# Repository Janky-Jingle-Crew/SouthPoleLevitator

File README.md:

# South Pole Levitator

Janky Jingle Crew is back this Christmas as well! We are continuing with the theme of magnetic propulsion from last year, but this time for levitation! 

## Background
Magnetic levitation kits have been around for a long time, but most of them are analog designs running on 12 V. A more recent 5 V digital version by [Jonathan Lock](https://gitlab.com/e4870/maglev/-/tree/main) caught our attention and served as a big source of inspiration for this project. Our take focuses on lowering the BOM cost and making assembly easier by replacing traditional coils with PCB coils.

We were aiming to build a batch of around 50 units, so coil winding quickly became a bottleneck. That led us to PCB coils as a more scalable solution. Mounting the coils was another pain point, gluing them down and then soldering wires (like many existing kits do) felt messy. Instead, we combined the mounting and electrical connection using solderable standoffs.

We also made a (slightly unnecessary) optimization on the microcontroller side. To reduce BOM cost slightly, we chose the STM32G030, which doesn’t have an FPU, and planned to implement all control algorithms using fixed-point math. In hindsight, the time spent probably outweighed the cost savings, but at least we learned a lot about fixed-point math (and wrote terrible code) along the way.

The final result is shown below: a fully functional magnetic levitation platform made entirely from PCBs. Even the levitating tree is a PCB. Overall, the project turned out well, although there are plenty of things that could still be improved. Feel free to open an issue or mail us if you have any technical questions.

<!--  -->

## User Guide

The card needs to be powered with a 5V power supply over USB-C, capable of at least 500 mA.

To levitate the tree:

1. Place the tree away from the driver board.
2. Place the driver board on a flat, nonmagnetic surface, and plug in the USB-C cable. Note that the board needs to be level when it gets power for the correct calibration. If the tree is too close, this will also affect the calibration. The calibration is complete once you hear a short beep from the coils. The status LED should also start blinking.
3. Hold the tree a few centimeters over and lower it slowly, trying to keep it centered and pointed straight up.
4. The rest is a balance between keeping the tree centered, and holding it with a loose enough grip. The tree needs to have the freedom to find the center itself, while also being prevented from sticking to either of the four base magnets.

It is also possible to play some Christmas tunes. Simply turn the driver board upside down and place the tree on top of it. The coils should start playing a random assortment of Christmas tunes.

## Working principle

### Magnetic levitation
The levitation is generated by four PCB coils but also four neodymium magnets. The base magnets provide the majority of the force required for levitation while the coils only generate a small corrective force required to keep the magnet in a stable position (Earnshaw's theorem). 

Each coil can be driven independently, but we chose to split the coils into two pairs (X & Y) and drive them with opposite polarity.

A 3D Hall effect sensor TMAG5273 was used to sense the position of the levitating magnet and drive the coils accordingly.

### Control

At the core the control algorithm is a PD controller controlling the duty cycle of the coil drivers in order to keep the levitating magnet centered in the X and Y direction. The position is not directly measured, instead the magnetic field strength in the X and Y direction is used as a proxy for position. This is not linear with the actual position, but is approximated as linear close to the center. This is the general idea but there are multiple problems that need to be handled for stable levitation:
<!-- - Non-linear relation between coil driver duty cycle and generated magnetic field. -->
<!-- - Non-linear coil driver characteristics. -->
<!-- - Coupling between coil current and measured magnetic field. -->
<!-- - Setpoint calibration. -->

<details>
<!-- #### Non-linear coil driver characteristics. -->
<summary> Non-linear coil driver characteristics </summary>

We observed a non linear relation between the coil driver duty cycle and the output current which can be seen in the figure below. To correct for this we wanted to measure the coil current as a function of duty cycle. Since coil current is proportional to the generated magnetic field we can measure the strength of the magnetic field for different duty cycles with the hall sensor. From this a quadratic fit was made which is used to linearize the coil driver response in the control algorithm.

</details>

<details>
<!-- #### Coil coupling compensation -->
<summary> Coupling between coil current and measured magnetic field </summary>

When driving the coils, the generated magnetic field affects the hall sensor measurements. This is problematic since this is added to the field from the levitating magnet and affects the position measurement. Since the position measurement is used as the input to the controller this creates a feedback loop which can lead to instability and oscillations. To compensate for this an feedforward model of the generated magnetic field from the coil current is subtracted from the hall sensor measurements before they are used in the controller. This model is created by measuring the magnetic field from each coil at different duty cycles while there is no levitating magnet present. A linear fit is then made to get the coupling coefficients for each coil. This is done during the initialization of the system.

</details>

<details>
<!-- #### Setpoint calibration -->
<summary> Setpoint calibration </summary>

Due to manufacturing tolerances in the placement of the hall sensor and the base magnets, the center of the base magnetic field, which is the optimal place to levitate the magnet, does not necessarily correspond to above the hall sensor. This means that the setpoint for the controller has to be calibrated for each unit.

In the figure above, an illustrative example of the magnetic potential from the base magnets and the proportional part of the PD controller is shown. The blue curve represents the potential from the base magnets, which has a unstable equilibrium point at $x_{base}=1$. The orange curve represents the potential from the proportional part of the controller, which is centered around the setpoint at $x_{setpoint} = 0$. The total potential is the sum of these two potentials, shown in green, which has a stable equilibrium point close to but not exactly at the setpoint. Due to the slope of the base potential at the setpoint, the equilibrium point will be offset the setpoint away from the base magnet center. By calculating this difference $x_{delta} = x_{equilibrium} - x_{setpoint}$ we can then adjust the setpoint $x_{setpoint,new} = x_{setpoint} + \alpha x_{delta}$ to move the equilibrium point closer to the setpoint. This process is repeated every control loop and will lead to the setpoint converging to the base magnet center.

</details>

### Driving LEDs wirelessly

The LEDs on the tree are powered by electro-magnetic noise from the switching ripple of the coils on the driver board. There are four PCB coils in the base of the tree, each powering its quarter. The induced AC voltage in each of these coils is amplified with a resonant LC-tank tuned to the switching frequency. The resonance circuit consists of the inductance in the PCB coil and a separate MLCC C0G capacitor on the tree quarter. This amplified waveform is then rectified with a single Schottky diode, finally driving the LEDs. The power transfer efficiency is absolutely garbage and therefore the LEDs will only light up when the coils are aligned. However, this also gives a passive blinking/strobing effect when it spins (without any additional components)! Definitely a planned feature and not a design flaw....

## Design
The whole levitator can be split into two main parts. The platform base and the levitating tree. The platform base consists of two different PCB designs, one driver PCB and four coil PCBs (4x).

### Driver board
The driver board has all the components mounted. There are a total of 12 standoffs: 8x M2 standoffs for mounting the coil board and 4x M3 standoffs for mounting the base magnets. An STM32G030 reads the XYZ magnetic fields from the TMAG5273 and controls 4x DRV8837 drivers for the coils. Power is provided by USB-C connector. A TagConnect TC2030 along with pin headers break out the SWD pins for debugging.

### Coil board
The coil board consists of four spiral coils with ~116 turns and 0.245mm trace width (25 turns per layer, 4-layer PCB, outer 1 oz, inner 1 oz). The resulting coil resistance turns out to be around 20 Ohm. Therefore, 4x coils are connected in parallel to enable higher coil current and also increase efficiency slightly. Brass washers are placed in-between each coil board to ensure electrical contact all the way down to the driver board. Initially a coil with 100 turns and 0.3mm trace width was used (outer 1 oz, inner 0.5 oz). This worked fine as well and 0.5oz is way cheaper. You can use either one, although the code might be slightly more tuned for the 116 turns variant, it should still work with the cheaper 100 turns variant.

### Tree
The tree consists of 5 PCBs, four of which constitute the tree itself, and one being the base plate with the pickup coils. A 3D-printed star keeps all of the tree-PCBs connected at the top! Tip: blow on one side of the tree when it is levitating to make it spin!

## Manufacturing
All the manufacturing files for the PCBs and the final software can be found in this repository. 

Upload these to your favorite PCB manufacturer and order the boards. We designed the boards with JLCPCBs preexisting Parts Lib and used their PCBA due to time constraints. However, PCBWay and NextPCB probably have these components in stock as well or can source them for you.

You will also need the following materials per unit:
- 1x Levitation magnet (N35-N45 30mm diameter, 10mm height) 
- 4x Ring magnets with M3 countersunk hole (N35-N45, 12mm diameter, 5mm height)
- 8x Non-magnetic M2 screws 8mm
- 4x Non-magnetic M3 countersunk screws 8mm
- 24x M2 Brass washers 4-5mm OD (steel probably works as well, slightly worse conductivity).
- 8x Rubber feet (at least 0.4mm height)

## Assembly

### Driver board

### Tree

To begin with, the star is 3D-printed. You can either use the half-star variant (recommended) or the whole-star variant. For the half-star, print two of them laying flat and with support activated. The halves can then be glued together with superglue. Alternatively, the whole-star variant can be printed standing up depending on how well your printer handles overhang and/or surface finishes over supports.

To keep the magnet centered, and the parts of the tree perpendicular to the base, a 3D-printed jig was used. This is not necessary, but drastically reduces the time to assemble multiple trees. If you are only making one, don't bother printing out the jig.

Both the magnet and the star can be glued with e.g. superglue or epoxy. Note that the magnet orientation matters!

The four "quarters" of the tree are soldered onto the base PCB with two solder joints each. These joints are the PCB coil A & B. We recommend gluing the star before soldering!

## FAQ

### How do I reproduce this?
PCB assembly files can be found in /production for the driver board and tree in their respective folders under PCB/. 
Gerber files for both coil boards are found in /gerber in their respective folders under PCB/. Remember to choose 1oz inner layers if you go for 116 turns variant.
Upload to your PCB manufacture of choice (JLCPCB, PCBWay, NextPCB).
Print the star. Buy magnets and screws. Assemble.

#### Flashing
An STLink, Segger Jlink or similar is required to flash the driver board. Some type of 6 pin (2x3 1.27mm pitch) pogo connector is also required (we use a TagConnect TC2030NL).
Or you can use the through hole SWD pins. A compiled binary is provided in SW/release if you don't want to go through the hassle of compiling yourself because the makefile is a bit of mess currently. It's written for a Windows filesystem but uses unix commands (we used msys2 or cmder to compile). Next project will probably use cmake to avoid these problems.

### How much did this all cost?
This year's project was quite expensive. Even with a big batch of 50 units, the unit cost was around 40-50 EUR. PCBs alone cost 20 EUR per unit. Magnets and screws were not cheap either.
Expect to spend quite a bit if you are planning on reproducing it, especially a small batch. 

## Acknowledgements
Special thanks to Jonathan Lock, this project was heavily inspired by his well-documented [maglev build](https://gitlab.com/e4870/maglev/-/tree/main).

Also thanks to Seth.K and his [coil generator plugin for KiCAD](https://github.com/SK-Electronics-Consulting/kicad-coil-generators). 

## Credits
The Janky Jingle Crew 2025 consists of:

 - [Daniel Quach](https://github.com/BasementCircuits): Project lead, PCB, Firmware
 - [Johan Wheeler](https://github.com/johanwheeler): Firmware, Control
 - [Gustav Abrahamsson](https://github.com/GustavAbrahamsson): PCB, Mechanical
 - [Adam Anderson](https://github.com/adaand00): Firmware

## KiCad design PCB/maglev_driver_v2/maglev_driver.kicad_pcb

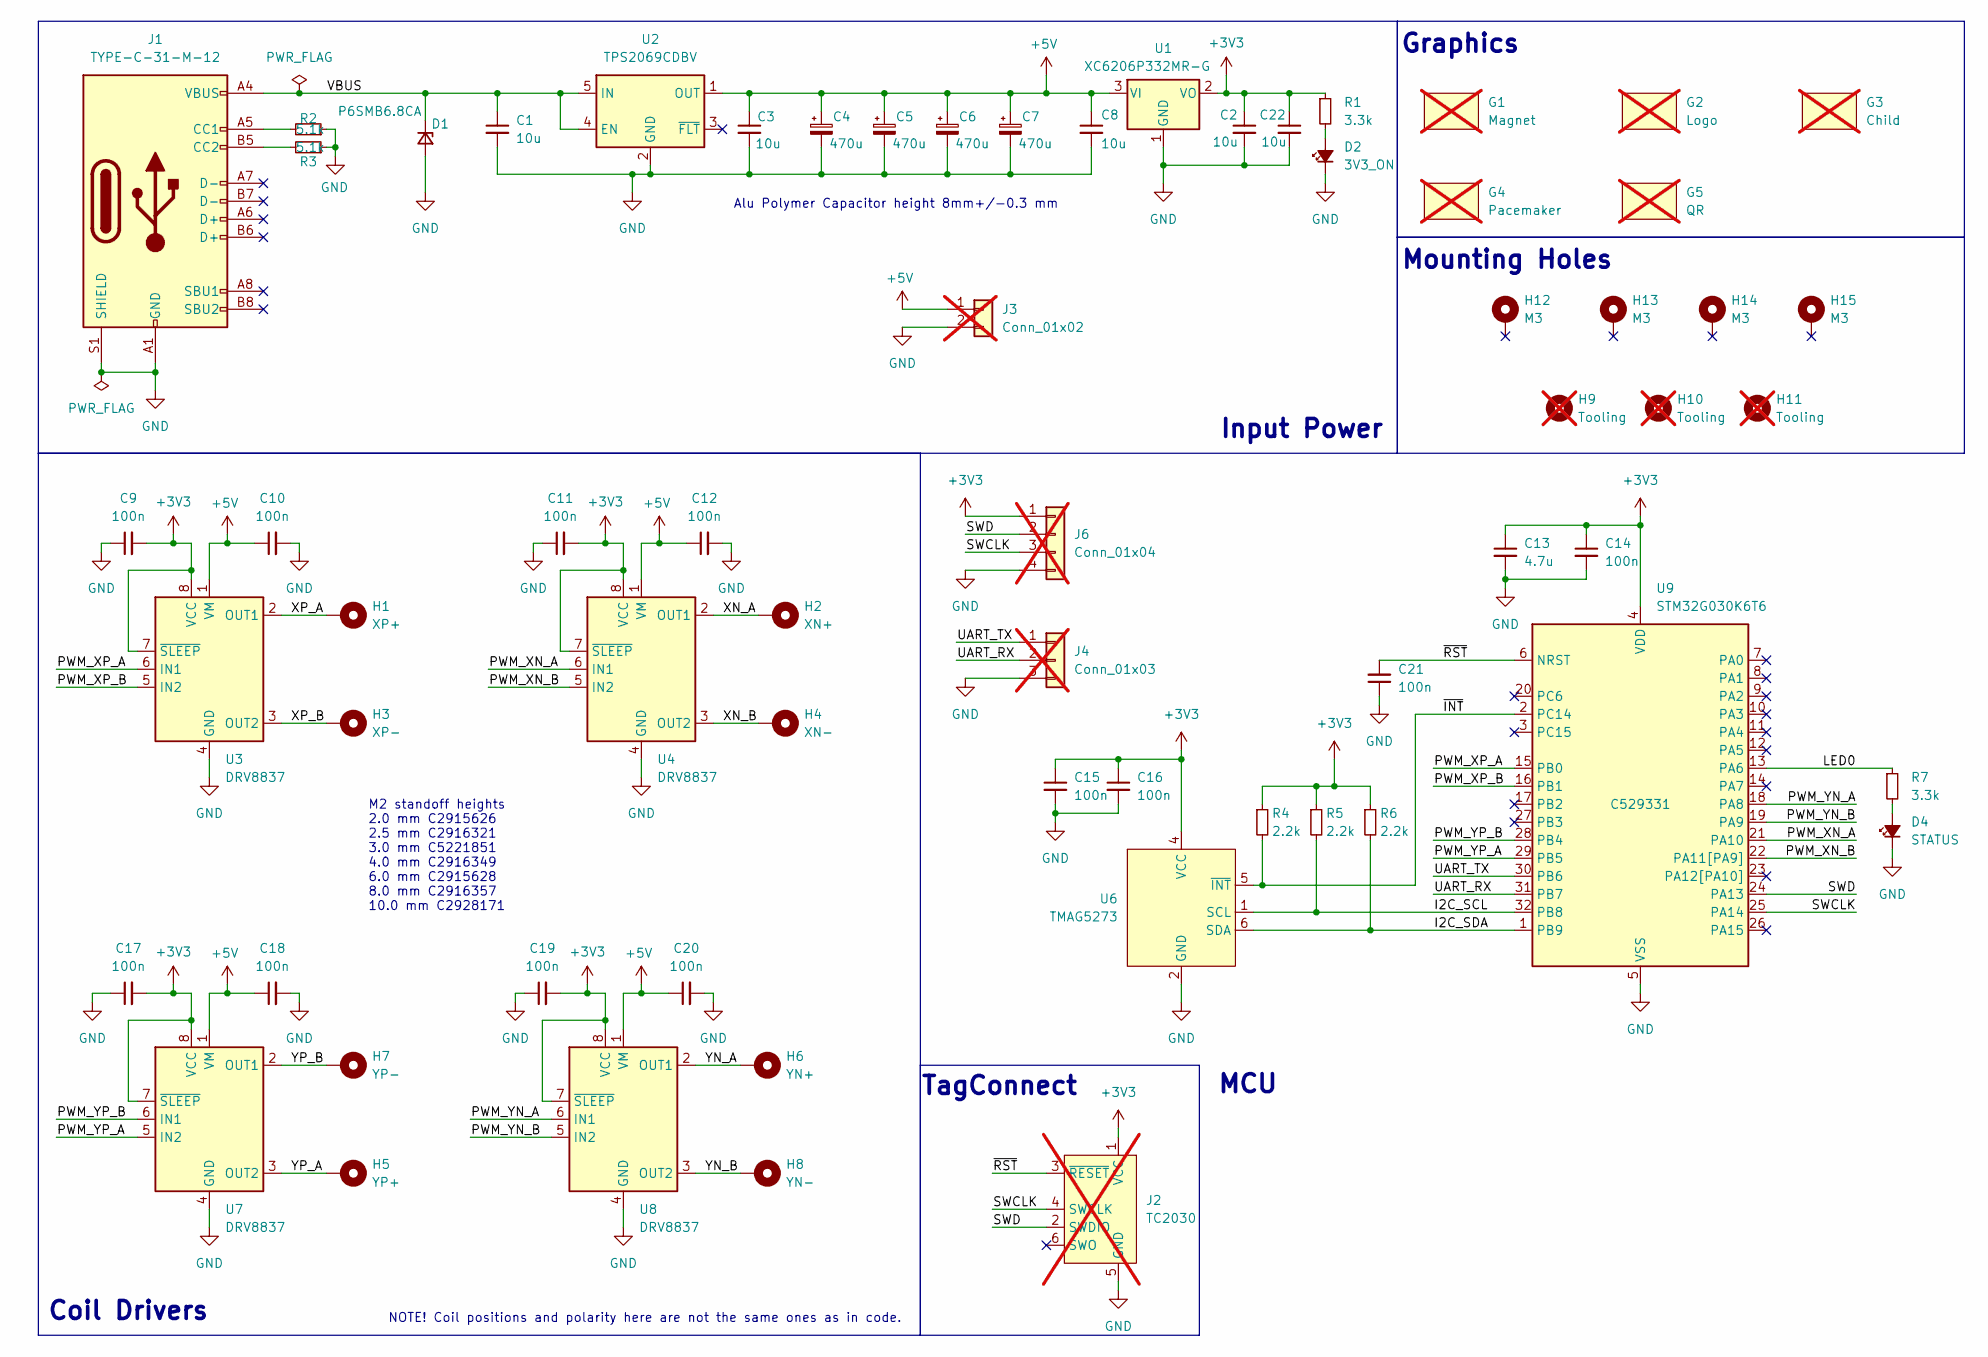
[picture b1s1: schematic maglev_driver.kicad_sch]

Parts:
C1, C2, C3, C8, C22: 10u; C_1206_3216Metric; MPN C13585
C4, C5, C6, C7: 470u; C_Elec_6.3x7.7; MPN C46550459
C9, C10, C11, C12, C14, C15, C16, C17, C18, C19, C20, C21: 100n; C_0402_1005Metric; MPN C307331
C13: 4.7u; C_1206_3216Metric; MPN C29823
D1: P6SMB6.8CA; D_SMB; MPN C78395
D2: 3V3_ON; LED_0805_2012Metric; MPN C2296
D4: STATUS; LED_0805_2012Metric; MPN C2297
G1: Magnet; mag_warning_7_7_mm; not fitted
G2: Logo; tree_7_9; not fitted
G3: Child; child_warning_7_8_mm; not fitted
G4: Pacemaker; pacemaker_warning_7_7_mm; not fitted
G5: QR; qr_25mm; not fitted
H1: XP+; SMTSO20; MPN C2928171
H2: XN+; SMTSO20; MPN C2928171
H3: XP-; SMTSO20; MPN C2928171
H4: XN-; SMTSO20; MPN C2928171
H5: YP+; SMTSO20; MPN C2928171
H6: YN+; SMTSO20; MPN C2928171
H7: YP-; SMTSO20; MPN C2928171
H8: YN-; SMTSO20; MPN C2928171
H9, H10, H11: Tooling; tooling_hole; not fitted
H12, H13, H14, H15: M3; SMTSO30; MPN C2915635
J1: TYPE-C-31-M-12; USB_C_Receptacle_HRO_TYPE-C-31-M-12; MPN C165948
J2: TC2030; Tag-Connect_TC2030-IDC-NL_2x03_P1.27mm_Vertical; not fitted
J3: Conn_01x02; PinHeader_1x02_P2.54mm_Vertical; not fitted
J4: Conn_01x03; PinHeader_1x03_P2.54mm_Vertical; not fitted
J6: Conn_01x04; PinHeader_1x04_P2.54mm_Vertical; not fitted
R1, R7: 3.3k; R_0402_1005Metric; MPN C25890
R2, R3: 5.1k; R_0603_1608Metric; MPN C23186
R4, R5, R6: 2.2k; R_0402_1005Metric; MPN C25879
U1: XC6206P332MR-G; SOT-23-3; MPN C5446
U2: TPS2069CDBV; SOT-23-5; MPN C181752
U3, U4, U7, U8: DRV8837; WSON-8-1EP_2x2mm_P0.5mm_EP0.9x1.6mm; MPN C39159
U6: TMAG5273; SOT-23-6; MPN C3716049
U9: STM32G030K6T6; LQFP-32_7x7mm_P0.8mm; MPN C529331

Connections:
+3V3: C2.1, C9.2, C11.2, C13.1, C14.1, C15.1, C16.1, C17.2, C19.2, C22.1, J2.1 (VCC), J6.1, R1.1, R4.1, R5.1, R6.1, U1.2 (VO), U3.7 (~SLEEP), U3.8 (VCC), U4.7 (~SLEEP), U4.8 (VCC), U6.4 (VCC), U7.7 (~SLEEP), U7.8 (VCC), U8.7 (~SLEEP), U8.8 (VCC), U9.4 (VDD)
+5V: C3.1, C4.1, C5.1, C6.1, C7.1, C8.1, C10.1, C12.1, C18.1, C20.1, J3.1, U1.3 (VI), U2.1 (OUT), U3.1 (VM), U4.1 (VM), U7.1 (VM), U8.1 (VM)
/I2C_SCL: R5.2, U6.1 (SCL), U9.32 (PB8)
/I2C_SDA: R6.2, U6.6 (SDA), U9.1 (PB9)
/LED0: R7.1, U9.13 (PA6)
/PWM_XN_A: U4.6 (IN1), U9.21 (PA10)
/PWM_XN_B: U4.5 (IN2), U9.22 (PA11[PA9])
/PWM_XP_A: U3.6 (IN1), U9.15 (PB0)
/PWM_XP_B: U3.5 (IN2), U9.16 (PB1)
/PWM_YN_A: U8.6 (IN1), U9.18 (PA8)
/PWM_YN_B: U8.5 (IN2), U9.19 (PA9)
/PWM_YP_A: U7.5 (IN2), U9.29 (PB5)
/PWM_YP_B: U7.6 (IN1), U9.28 (PB4)
/SWCLK: J2.4 (SWCLK), J6.3, U9.25 (PA14)
/SWD: J2.2 (SWDIO), J6.2, U9.24 (PA13)
/UART_RX: J4.2, U9.31 (PB7)
/UART_TX: J4.1, U9.30 (PB6)
/VBUS: C1.1, D1.1 (K), J1.A4 (VBUS), J1.A9 (VBUS), J1.B4 (VBUS), J1.B9 (VBUS), U2.4 (EN), U2.5 (IN)
/XN_A: H2.1, U4.2 (OUT1)
/XN_B: H4.1, U4.3 (OUT2)
/XP_A: H1.1, U3.2 (OUT1)
/XP_B: H3.1, U3.3 (OUT2)
/YN_A: H6.1, U8.2 (OUT1)
/YN_B: H8.1, U8.3 (OUT2)
/YP_A: H5.1, U7.3 (OUT2)
/YP_B: H7.1, U7.2 (OUT1)
/~INT: R4.2, U6.5 (~INT), U9.2 (PC14)
/~RST: C21.2, J2.3 (~RESET), U9.6 (NRST)
GND: C1.2, C2.2, C3.2, C4.2, C5.2, C6.2, C7.2, C8.2, C9.1, C10.2, C11.1, C12.2, C13.2, C14.2, C15.2, C16.2, C17.1, C18.2, C19.1, C20.2, C21.1, C22.2, D1.2 (A), D2.1 (K), D4.1 (K), J1.A1 (GND), J1.A12 (GND), J1.B1 (GND), J1.B12 (GND), J1.S1 (SHIELD), J2.5 (GND), J3.2, J4.3, J6.4, R2.1, R3.1, U1.1 (GND), U2.2 (GND), U3.4 (GND), U3.9 (GND), U4.4 (GND), U4.9 (GND), U6.2 (GND), U6.3 (GND), U7.4 (GND), U7.9 (GND), U8.4 (GND), U8.9 (GND), U9.5 (VSS)
unnamed: D2.2 (A), R1.2
unnamed: D4.2 (A), R7.2
unnamed: J1.A5 (CC1), R2.2
unnamed: J1.B5 (CC2), R3.2

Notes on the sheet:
NOTE! Coil positions and polarity here are not the same ones as in code.
MCU
Graphics
Coil Drivers
Alu Polymer Capacitor height 8mm+/-0.3 mm
M2 standoff heights 2.0 mm C2915626 2.5 mm C2916321 3.0 mm C5221851 4.0 mm C2916349 6.0 mm C2915628 8.0 mm C2916357 10.0 mm C2928171
Mounting Holes
TagConnect
Input Power

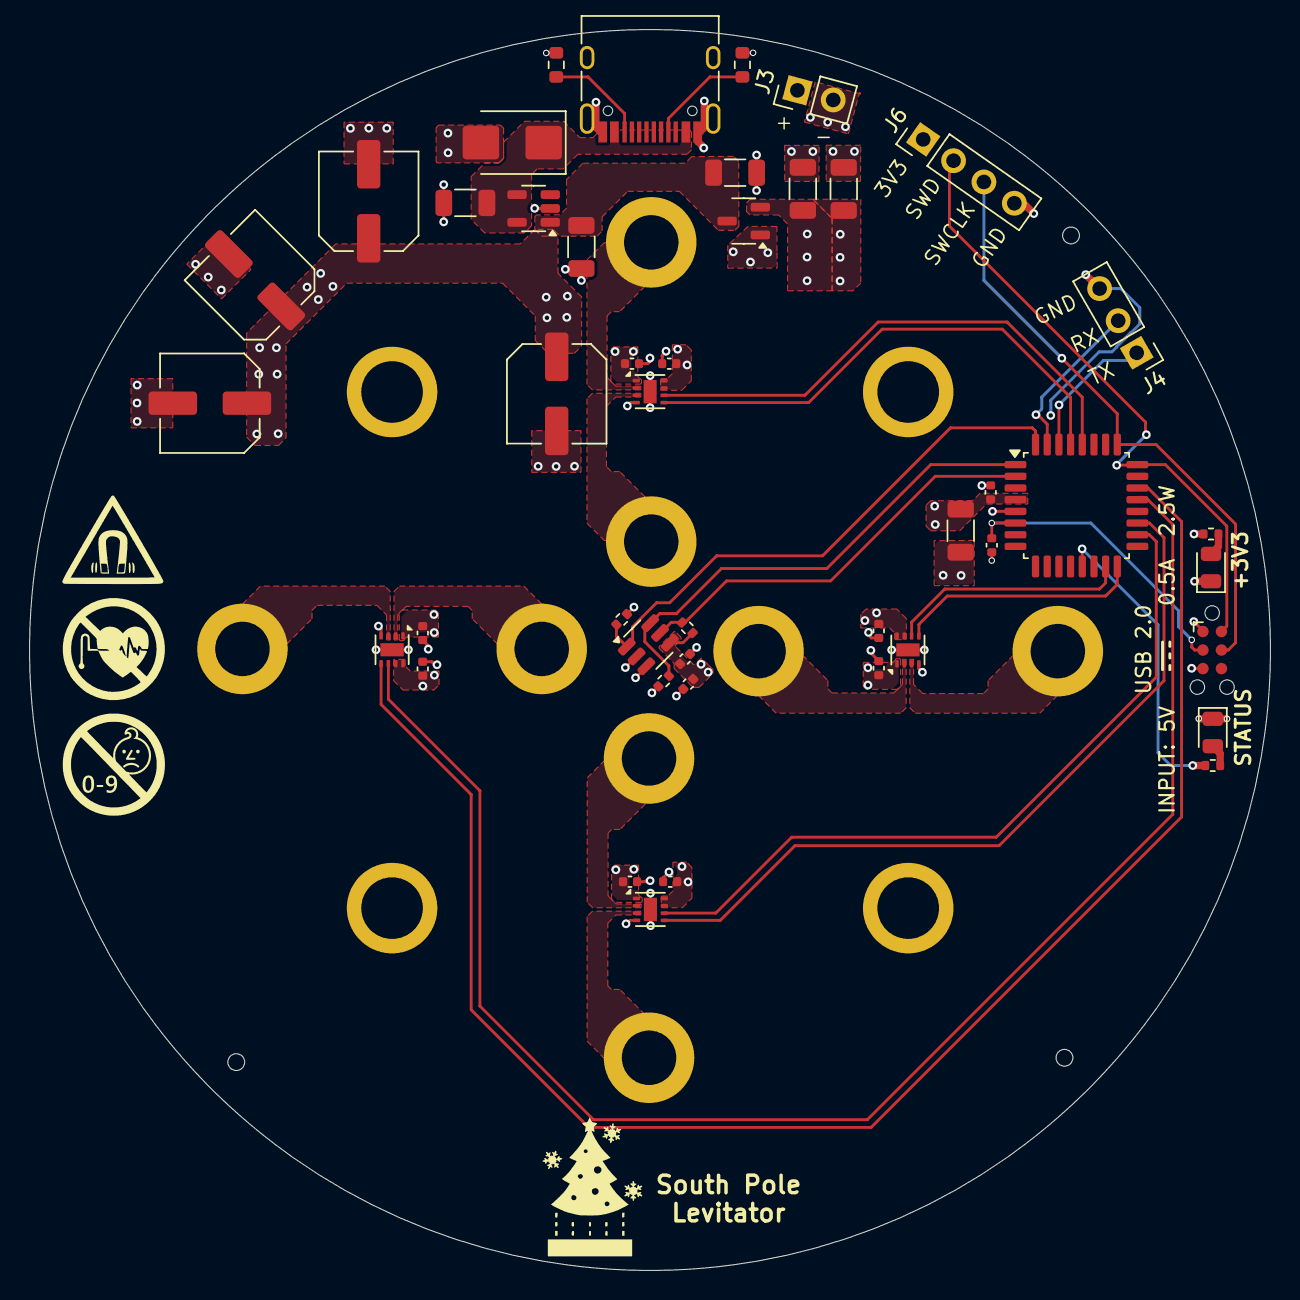
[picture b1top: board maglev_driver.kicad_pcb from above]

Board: 4 copper layers, 85.0 x 85.0 mm, 65 parts (1 on the bottom side), 33 nets.

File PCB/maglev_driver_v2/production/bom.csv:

Designator,Footprint,Quantity,Value,LCSC Part #
"C1, C2, C22, C3, C8",1206,5,10u,C13585
"C10, C11, C12, C14, C15, C16, C17, C18, C19, C20, C21, C9",0402,12,100n,C307331
C13,1206,1,4.7u,C29823
"C4, C5, C6, C7",C_Elec_6.3x7.7,4,470u,C46550459
D1,D_SMB,1,P6SMB6.8CA,C78395
D2,0805,1,3V3_ON,C2296
D4,0805,1,STATUS,C2297
H1,SMTSO20,1,XP+,C2928171
"H12, H13, H14, H15",SMTSO30,4,M3,C2915635
H2,SMTSO20,1,XN+,C2928171
H3,SMTSO20,1,XP-,C2928171
H4,SMTSO20,1,XN-,C2928171
H5,SMTSO20,1,YP+,C2928171
H6,SMTSO20,1,YN+,C2928171
H7,SMTSO20,1,YP-,C2928171
H8,SMTSO20,1,YN-,C2928171
J1,USB_C_Receptacle_HRO_TYPE-C-31-M-12,1,TYPE-C-31-M-12,C165948
"R1, R7",0402,2,3.3k,C25890
"R2, R3",0603,2,5.1k,C23186
"R4, R5, R6",0402,3,2.2k,C25879
U1,SOT-23-3,1,XC6206P332MR-G,C5446
U2,SOT-23-5,1,TPS2069CDBV,C181752
"U3, U4, U7, U8",WSON-8-1EP_2x2mm_P0.5mm_EP0.9x1.6mm,4,DRV8837,C39159
U6,SOT-23-6,1,TMAG5273,C3716049
U9,LQFP-32_7x7mm_P0.8mm,1,STM32G030K6T6,C529331

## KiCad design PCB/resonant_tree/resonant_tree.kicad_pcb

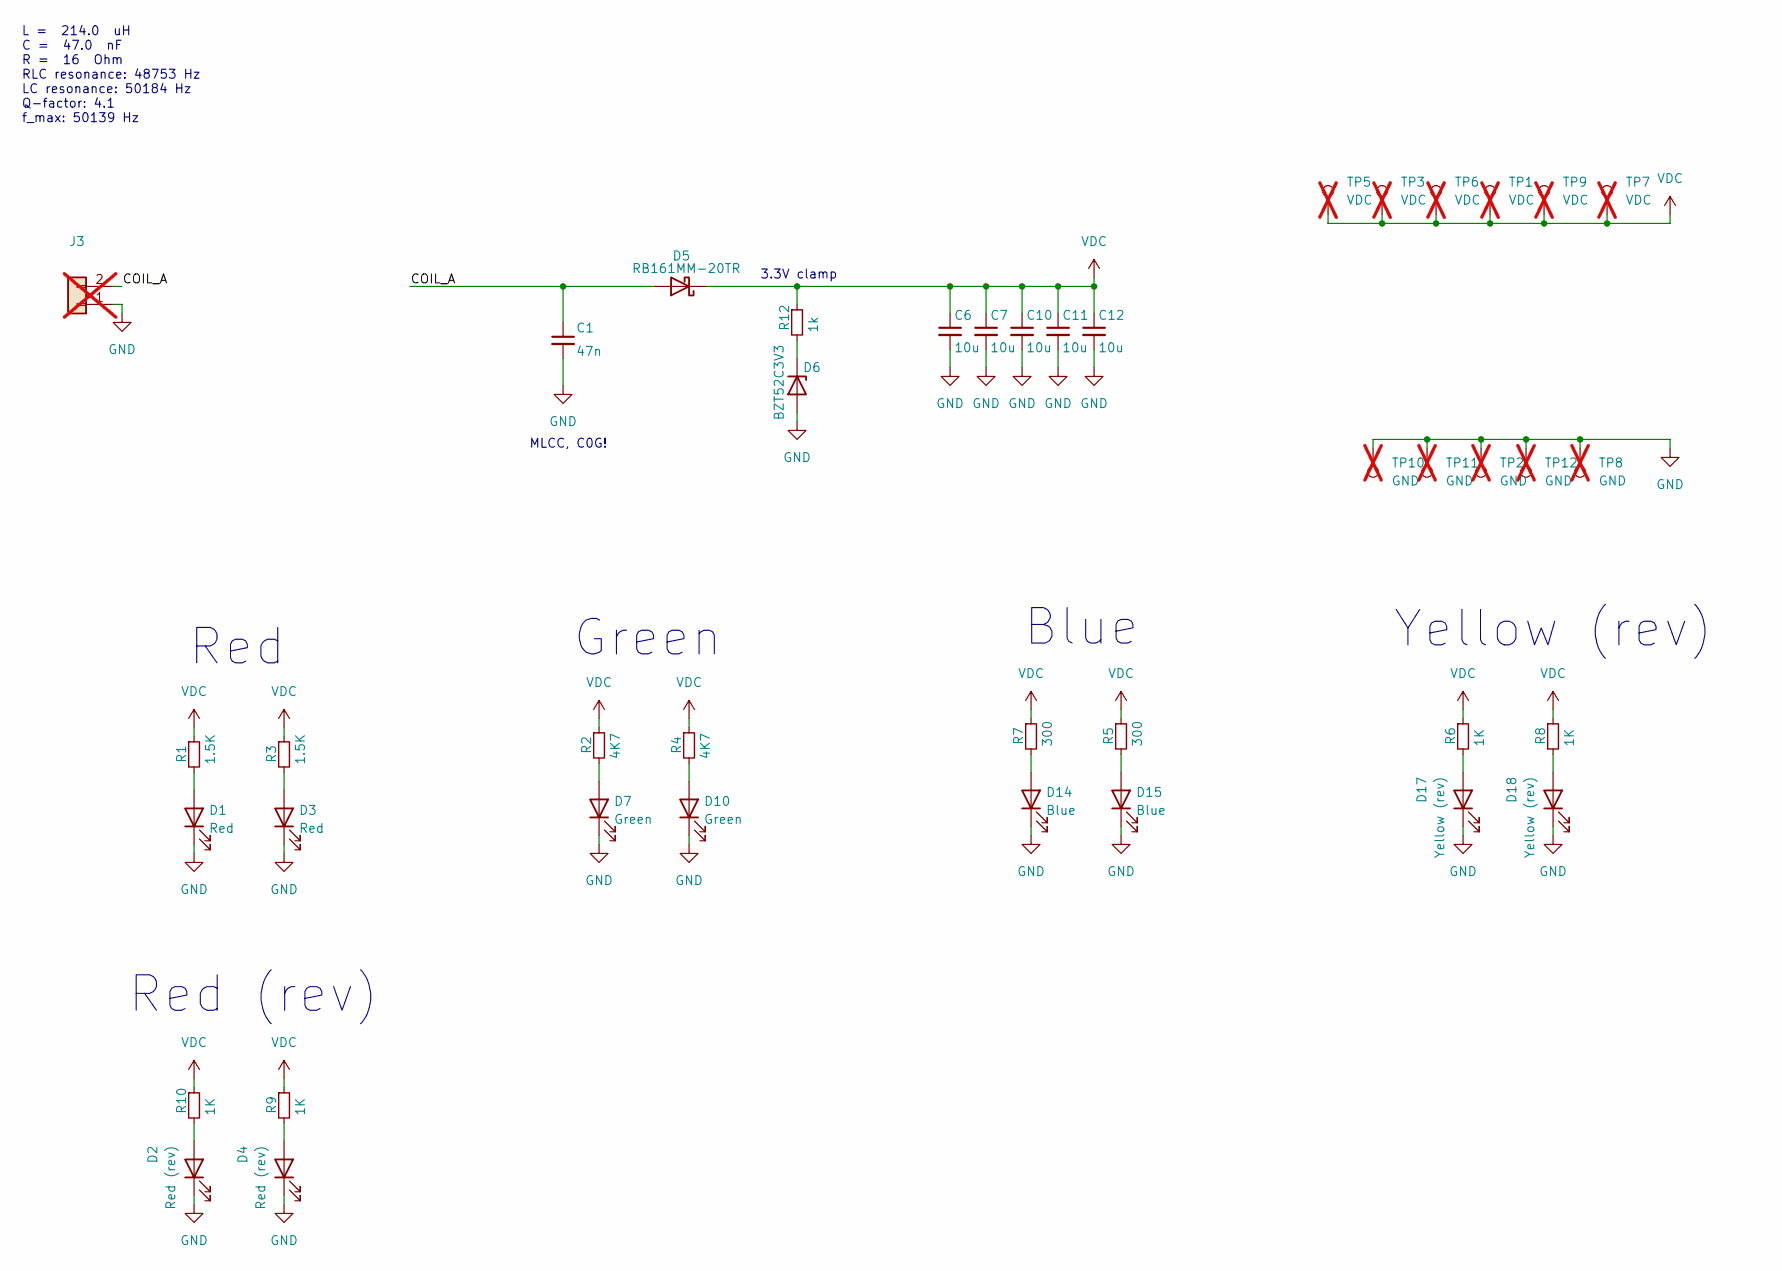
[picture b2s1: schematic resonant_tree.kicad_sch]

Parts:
C1: 47n; C_1206_3216Metric; MPN C21812
C6, C7, C10, C11, C12: 10u; C_1206_3216Metric; MPN C13585
D1, D3: Red; LED_0603_1608Metric; MPN C2286
D2, D4: Red (rev); LED_1206_3216Metric_ReverseMount_Hole1.8x2.4mm; MPN C125107
D5: RB161MM-20TR; D_SOD-123F; MPN C123070
D6: BZT52C3V3; D_SOD-123; MPN C19077396
D7, D10: Green; LED_0805_2012Metric; MPN C2297
D14, D15: Blue; LED_0603_1608Metric; MPN C2288
D17, D18: Yellow (rev); LED_1206_3216Metric_ReverseMount_Hole1.8x2.4mm; MPN C125108
J3: tree_link; not fitted
R1, R3: 1.5K; R_0603_1608Metric; MPN C22843
R2, R4: 4K7; R_0603_1608Metric; MPN C23162
R5, R7: 300; R_0603_1608Metric; MPN C23025
R6, R8, R9, R10: 1K; R_0603_1608Metric; MPN C21190
R12: 1k; R_0603_1608Metric; MPN C21190
TP1, TP3, TP5, TP6, TP7, TP9: VDC; TestPoint_Pad_D2.0mm; not fitted
TP2, TP8, TP10, TP11, TP12: GND; TestPoint_Pad_D2.0mm; not fitted

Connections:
/COIL_A: C1.1, D5.2 (A), J3.2
GND: C1.2, C6.2, C7.2, C10.2, C11.2, C12.2, D1.1 (K), D2.1 (K), D3.1 (K), D4.1 (K), D6.2 (A), D7.1 (K), D10.1 (K), D14.1 (K), D15.1 (K), D17.1 (K), D18.1 (K), J3.1, TP2.1, TP8.1, TP10.1, TP11.1, TP12.1
unnamed: D1.2 (A), R1.2
unnamed: D2.2 (A), R10.2
unnamed: D3.2 (A), R3.2
unnamed: D4.2 (A), R9.2
unnamed: D6.1 (K), R12.2
unnamed: D7.2 (A), R2.2
unnamed: D10.2 (A), R4.2
unnamed: D14.2 (A), R7.2
unnamed: D15.2 (A), R5.2
unnamed: D17.2 (A), R6.2
unnamed: D18.2 (A), R8.2
VDC: C6.1, C7.1, C10.1, C11.1, C12.1, D5.1 (K), R1.1, R2.1, R3.1, R4.1, R5.1, R6.1, R7.1, R8.1, R9.1, R10.1, R12.1, TP1.1, TP3.1, TP5.1, TP6.1, TP7.1, TP9.1

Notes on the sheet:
Red
MLCC, C0G!
Blue
3.3V clamp
Yellow (rev)
Green
Red (rev)
L = 214.0 uH C = 47.0 nF R = 16 Ohm RLC resonance: 48753 Hz LC resonance: 50184 Hz Q-factor: 4.1 f_max: 50139 Hz

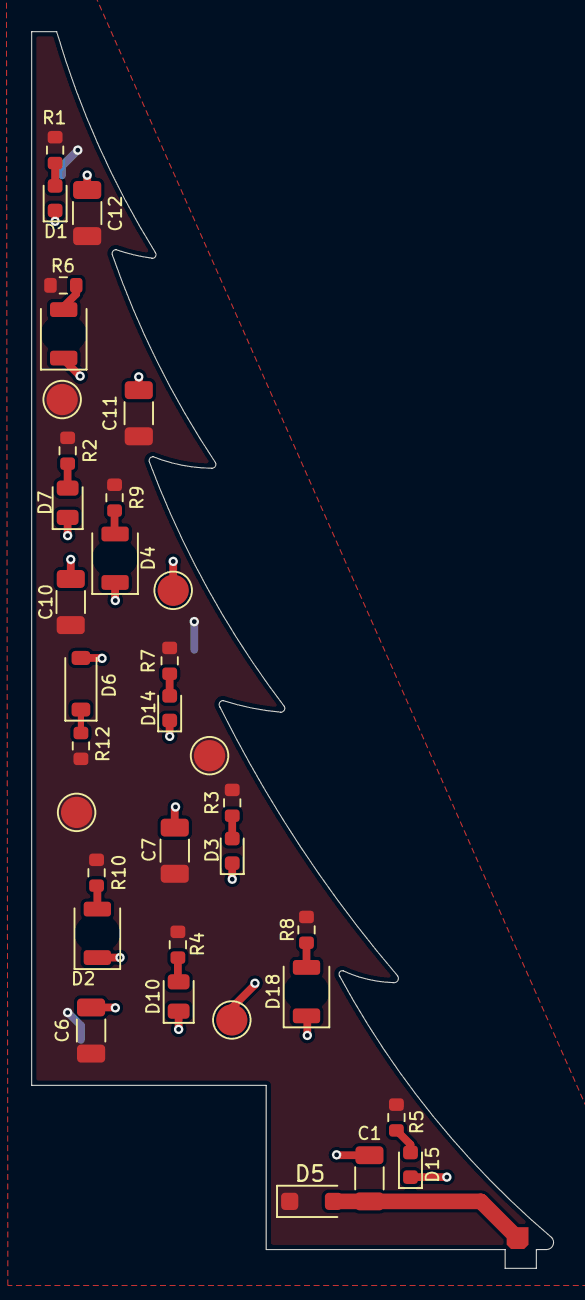
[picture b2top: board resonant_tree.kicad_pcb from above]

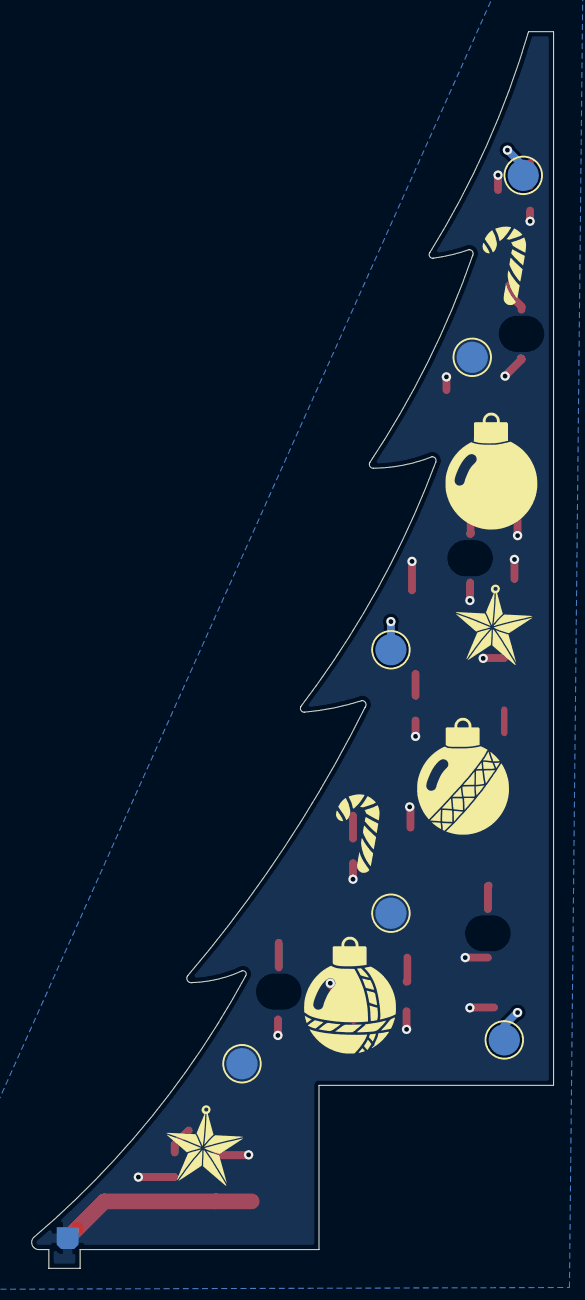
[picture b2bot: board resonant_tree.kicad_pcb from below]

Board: 2 copper layers, 33.4 x 79.1 mm, 41 parts (6 on the bottom side), 14 nets.

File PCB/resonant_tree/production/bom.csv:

Designator,Footprint,Quantity,Value,LCSC Part #
C1,1206,1,47n,C21812
"C10, C11, C12, C6, C7",1206,5,10u,C13585
"D1, D3",0603,2,Red,C2286
"D10, D7",0805,2,Green,C2297
"D14, D15",0603,2,Blue,C2288
"D17, D18",1206,2,Yellow (rev),C125108
"D2, D4",1206,2,Red (rev),C125107
D5,D_SOD-123F,1,RB161MM-20TR,C123070
D6,D_SOD-123,1,BZT52C3V3,C19077396
"R1, R3",0603,2,1.5K,C22843
"R10, R6, R8, R9",0603,4,1K,C21190
R12,0603,1,390,C23151
"R2, R4",0603,2,4K7,C23162
"R5, R7",0603,2,300,C23025

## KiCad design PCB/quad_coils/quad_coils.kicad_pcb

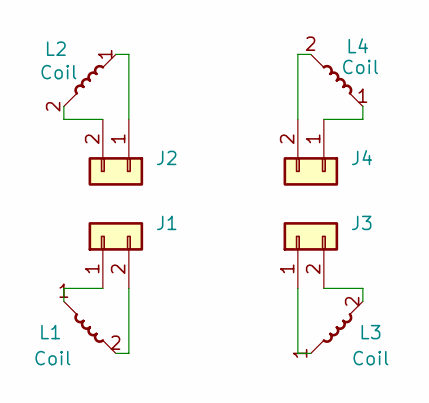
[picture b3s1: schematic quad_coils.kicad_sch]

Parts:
J1, J2, J3, J4: tree_mounting_point
L1, L2, L3, L4: Coil; 4L_100turns_33dia_0.3w

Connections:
unnamed: J1.1, L1.1
unnamed: J1.2, L1.2
unnamed: J2.1, L2.1
unnamed: J2.2, L2.2
unnamed: J3.1, L3.1
unnamed: J3.2, L3.2
unnamed: J4.1, L4.1
unnamed: J4.2, L4.2

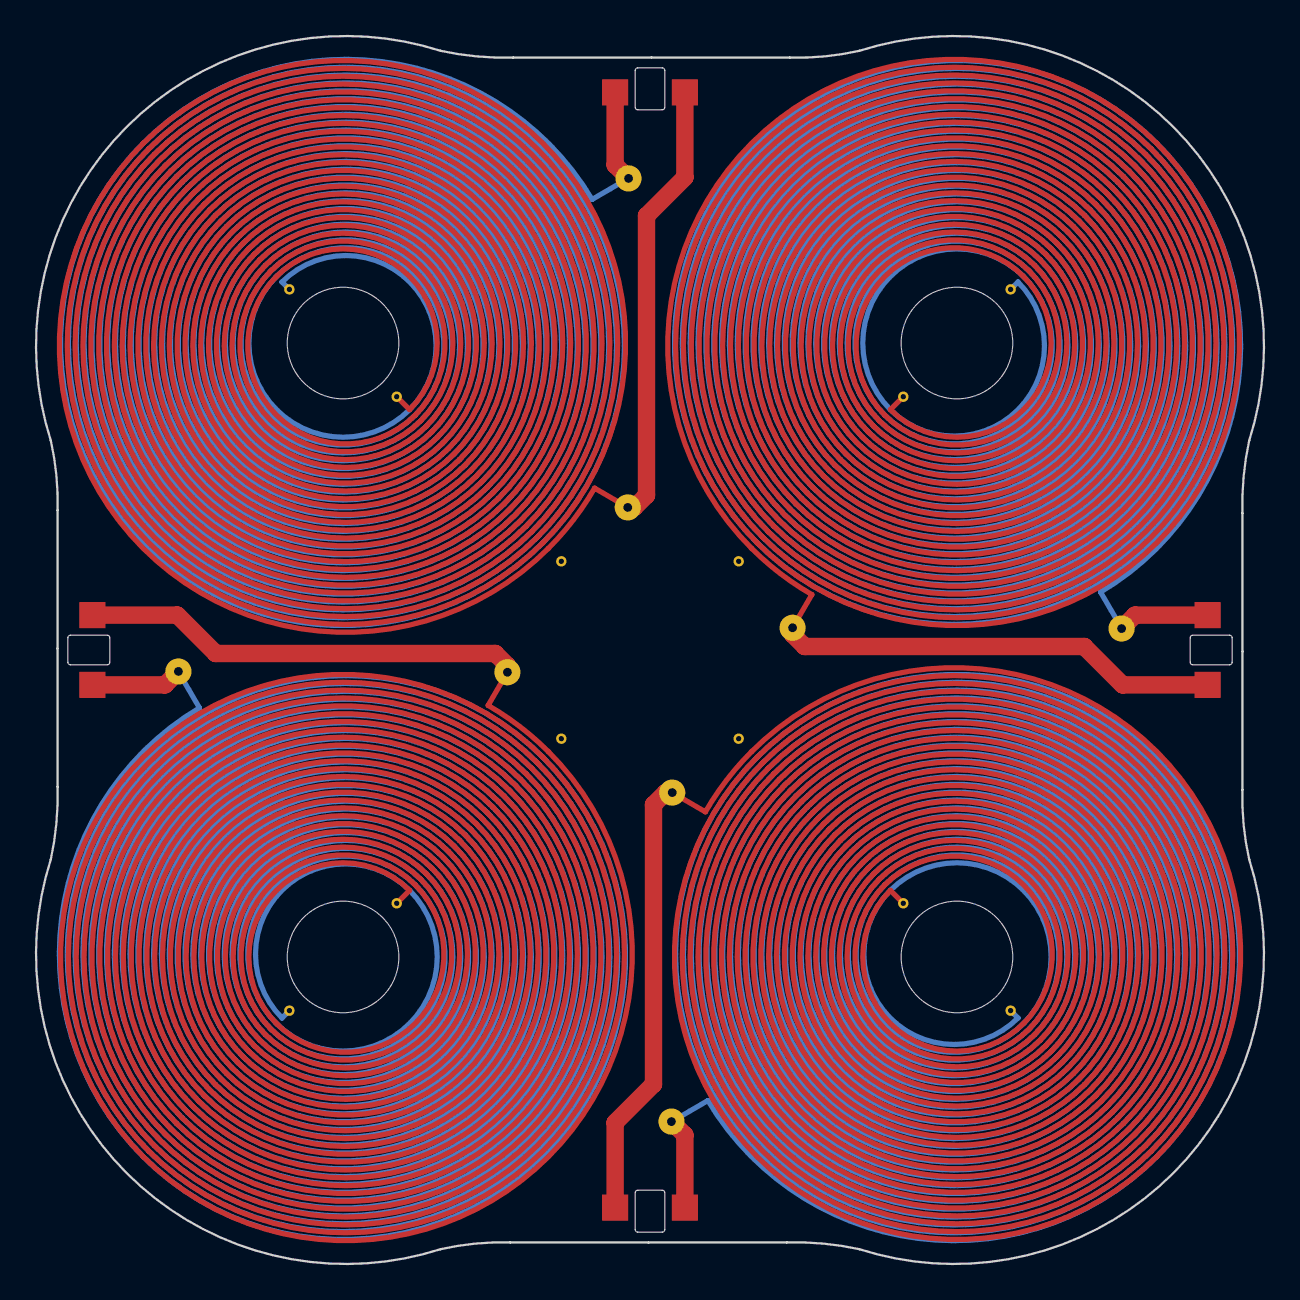
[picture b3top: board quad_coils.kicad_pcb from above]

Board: 4 copper layers, 70.4 x 70.4 mm, 8 parts (0 on the bottom side), 8 nets.

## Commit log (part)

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2025-12-17 Add PCBs and CAD
2026-01-03 Added driver board files
2026-01-03 Add pic and GIFs
2026-01-03 Add GIFs and update README
2026-01-04 Add coil board
2026-01-04 Add first release of SW
2026-01-04 Update .gitignore to exclude local vscode settings
